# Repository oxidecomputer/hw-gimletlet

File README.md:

# hw-gimletlet
More full-featured breakout board for the STM32H7, including many expansion headers for daughter boards. 

In active use for Hubris development and as a Swiss Army Knife around the lab.  Generally
when someone is speaking about a "gimletlet" the mean gimletlet2 "Glorified Gimletlet" as
a *vanishingly* small number of gimletlet1's were built and used for some very early network
bring-up.

Some [design notes](docs/gimletlet-2.mkdn) for gimletlet2
More [design notes](docs/gimletlet.mkdn) for gimletlet2

Some [mechanical specs](docs/gimletlet-mechanical.pdf)

# Bonus boards

## gimletlet-1
 The OG gimletlet.  Same CPU, nothing else is the same :)

*very limited use, very limited quantity*

[Subfolder](gimletlet1)

## management network bringup

*very limited use, very limited quantity*

Pairs with the gimletlet-1

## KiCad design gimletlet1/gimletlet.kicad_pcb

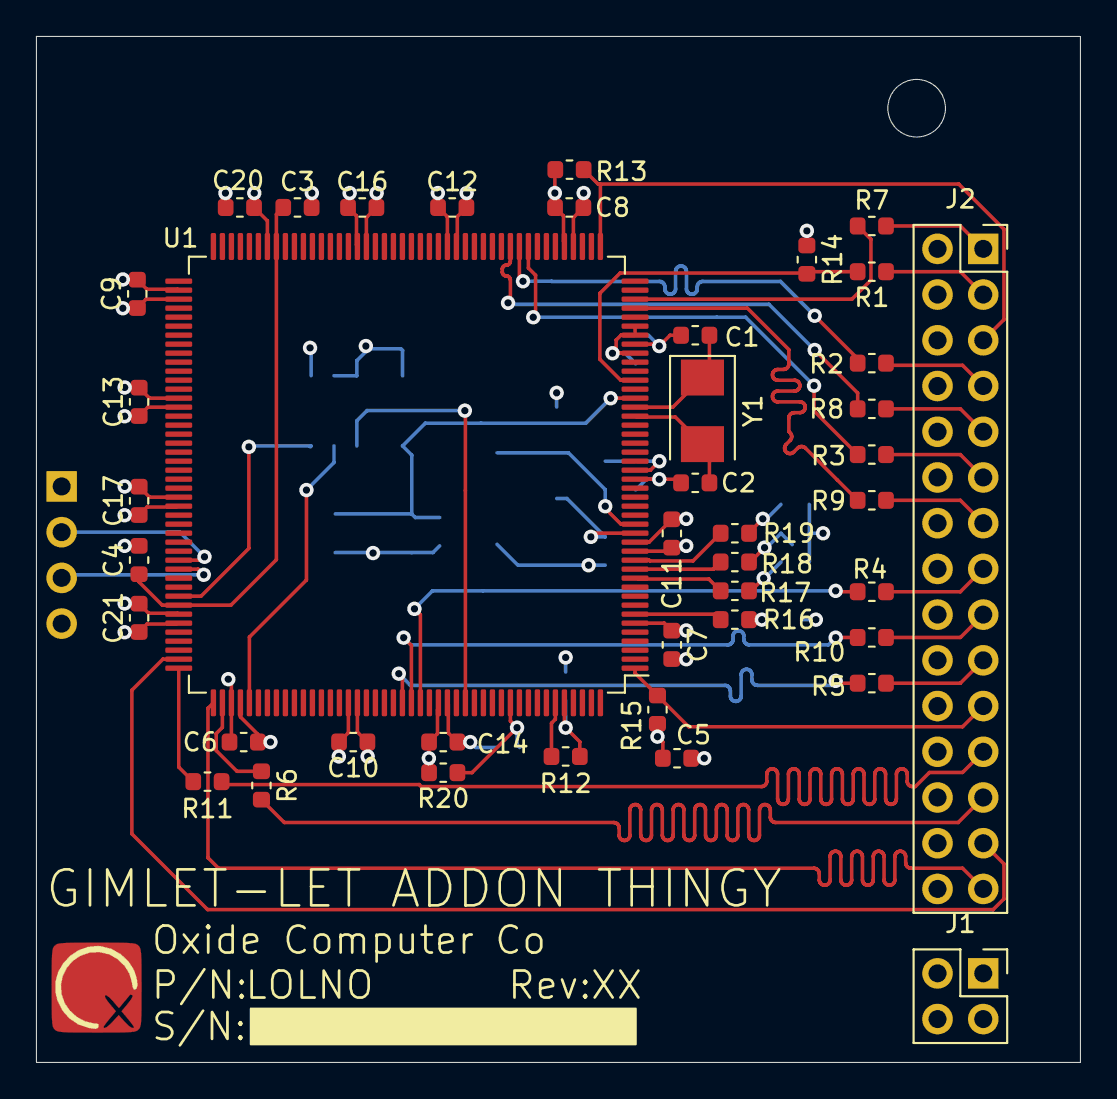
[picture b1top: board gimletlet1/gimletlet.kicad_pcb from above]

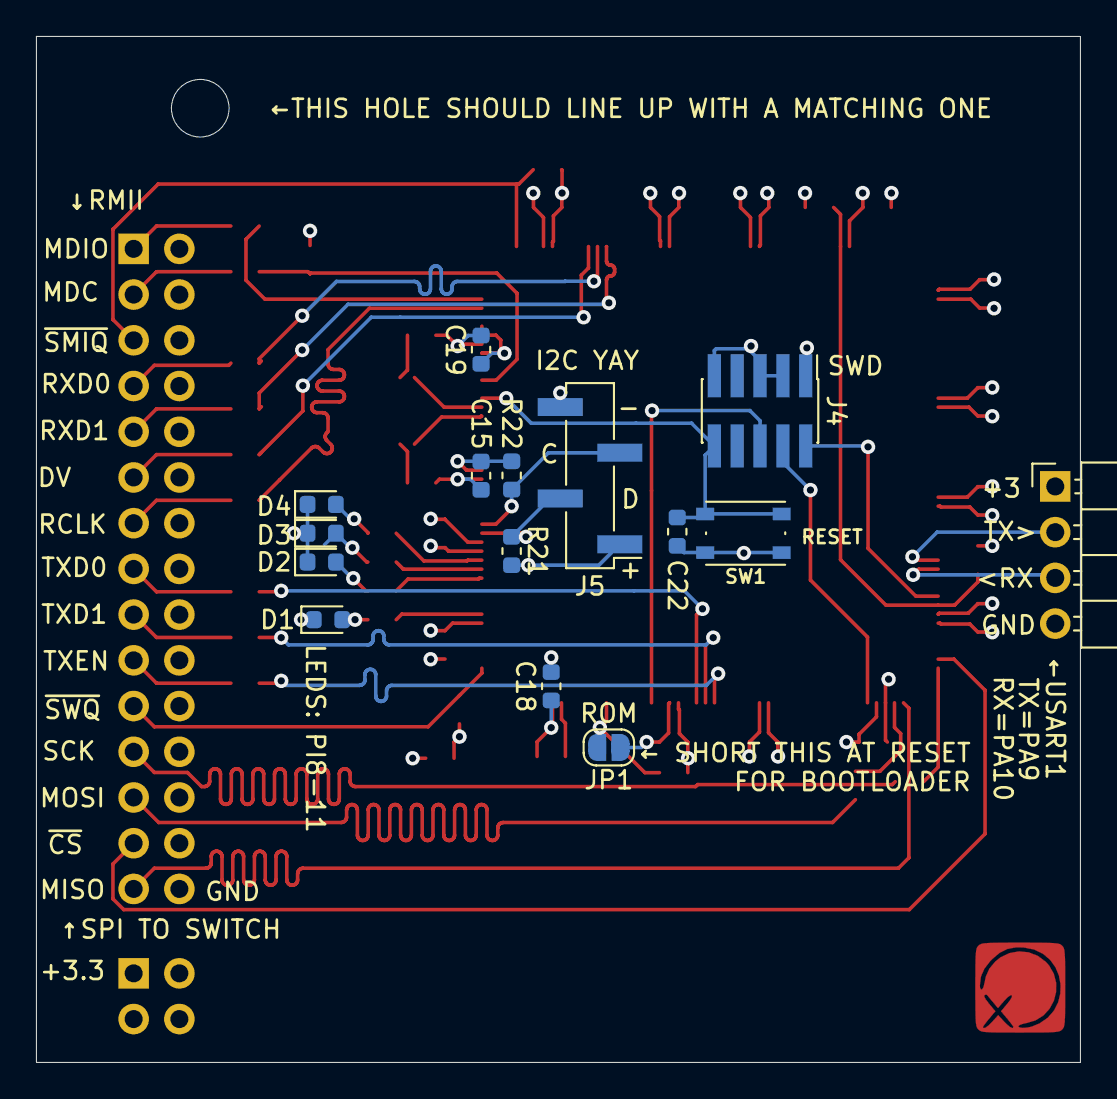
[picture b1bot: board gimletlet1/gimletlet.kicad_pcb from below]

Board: 4 copper layers, 58.0 x 57.0 mm, 59 parts (16 on the bottom side), 49 nets.

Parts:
C1, C2: 11p; C_0603_1608Metric
C3, C4: 2µ2 100mR; C_0603_1608Metric
C5: 4µ7; C_0603_1608Metric
C6, C7, C8, C9, C10, C11, C12, C13, C14, C15, C16, C17, C18, C19, C20, C21, C22: 0µ1; C_0603_1608Metric
D1, D2, D3, D4: LED; LED_0603_1608Metric
FID1: LOLNO; Oxide_Board_Identifier_33x7mm
H1: MountingHole; MountingHole_3.2mm_M3
J1: Conn_02x16_Odd_Even; PinSocket_2x02_P2.54mm_Vertical
J2: Conn_02x15_Odd_Even; PinSocket_2x15_P2.54mm_Vertical
J3: Conn_01x04; PinHeader_1x04_P2.54mm_Horizontal
J4: SWD; PinHeader_2x05_P1.27mm_Vertical_SMD
J5: I2C; PinHeader_1x04_P2.54mm_Vertical_SMD_Pin1Left
JP1: ROM; SolderJumper-2_P1.3mm_Open_RoundedPad1.0x1.5mm
R1, R2, R3, R4, R5, R6, R7, R8, R9, R10, R11: 22; R_0603_1608Metric
R12, R20, R21, R22: 10k; R_0603_1608Metric
R13, R14, R15: 100k; R_0603_1608Metric
R16, R17, R18, R19: 68; R_0603_1608Metric
SW1: RESET; PTS815
U1: STM32H753IITx; LQFP-176_24x24mm_P0.5mm
Y1: 8MHz; Crystal_SMD_5032-2Pin_5.0x3.2mm

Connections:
+3V3: C5.1, C6.1, C7.1, C8.1, C9.1, C10.1, C11.1, C12.1, C13.1, C14.1, C15.1, C16.1, C17.1, C18.1, C19.1, C20.1, C21.1, J1.1, J1.3, J3.1, J4.1, J5.1, JP1.1, R12.2, R13.1, R14.1, R15.1, R21.2, R22.2, U1.6, U1.15, U1.23, U1.36, U1.38, U1.39, U1.49, U1.62, U1.72, U1.82, U1.91, U1.103, U1.114, U1.127, U1.136, U1.149, U1.159, U1.172
/BOOT0: JP1.2, R20.1, U1.166
/LED0: R16.2, U1.7
/LED1: R17.2, U1.11
/LED2: R18.2, U1.12
/LED3: R19.2, U1.13
/MDC: R1.1, R14.2, U1.33
/MDIO: R7.1, U1.42
/OSC_IN: C2.1, U1.29, Y1.2
/OSC_OUT: C1.1, U1.30, Y1.1
/RMII_CRS_DV: R3.1, U1.53
/RMII_REF_CLK: R9.1, U1.41
/RMII_RXD0: R2.1, U1.54
/RMII_RXD1: R8.1, U1.55
/RMII_TXD0: R4.1, U1.156
/RMII_TXD1: R10.1, U1.155
/RMII_TXEN: R5.1, U1.154
/SCL: J5.3, R22.1, U1.17
/SDA: J5.2, R21.1, U1.16
/SPI2_MISO: J2.29, U1.133
/SPI2_MOSI: R6.1, U1.134
/SPI2_SCK: R11.1, U1.132
/SWCLK: J4.4, U1.137
/SWDIO: J4.2, U1.124
/SWO: J4.6, U1.161
/USART1_RX: J3.3, U1.121
/USART1_TX: J3.2, U1.120
/X_MDC: J2.3, R1.2
/X_MDIO: J2.1, R7.2
/X_RMII_CRS_DV: J2.11, R3.2
/X_RMII_REFCLK: J2.13, R9.2
/X_RMII_RXD0: J2.7, R2.2
/X_RMII_RXD1: J2.9, R8.2
/X_RMII_TXD0: J2.15, R4.2
/X_RMII_TXD1: J2.17, R10.2
/X_RMII_TXEN: J2.19, R5.2
/X_SPI_MOSI: J2.25, R6.2
/X_SPI_SCK: J2.23, R11.2
/~RST: C22.1, J4.10, SW1.1, U1.31
/~SMI_IRQ: J2.5, R13.2, U1.45
/~SPI2_CS0: J2.27, U1.131
/~SW_IRQ: J2.21, R15.2, U1.1
GND: C1.2, C2.2, C3.2, C4.2, C5.2, C6.2, C7.2, C8.2, C9.2, C10.2, C11.2, C12.2, C13.2, C14.2, C15.2, C16.2, C17.2, C18.2, C19.2, C20.2, C21.2, C22.2, D1.1, D2.1, D3.1, D4.1, J2.2, J2.4, J2.6, J2.8, J2.10, J2.12, J2.14, J2.16, J2.18, J2.20, J2.22, J2.24, J2.26, J2.28, J2.30, J3.4, J4.3, J4.5, J4.9, J5.4, R20.2, SW1.2, U1.14, U1.22, U1.37, U1.48, U1.61, U1.71, U1.90, U1.102, U1.113, U1.126, U1.135, U1.148, U1.158
unnamed: C3.1, C4.1, U1.81, U1.125
unnamed: D1.2, R16.1
unnamed: D2.2, R17.1
unnamed: D3.2, R18.1
unnamed: D4.2, R19.1
unnamed: R12.1, U1.171

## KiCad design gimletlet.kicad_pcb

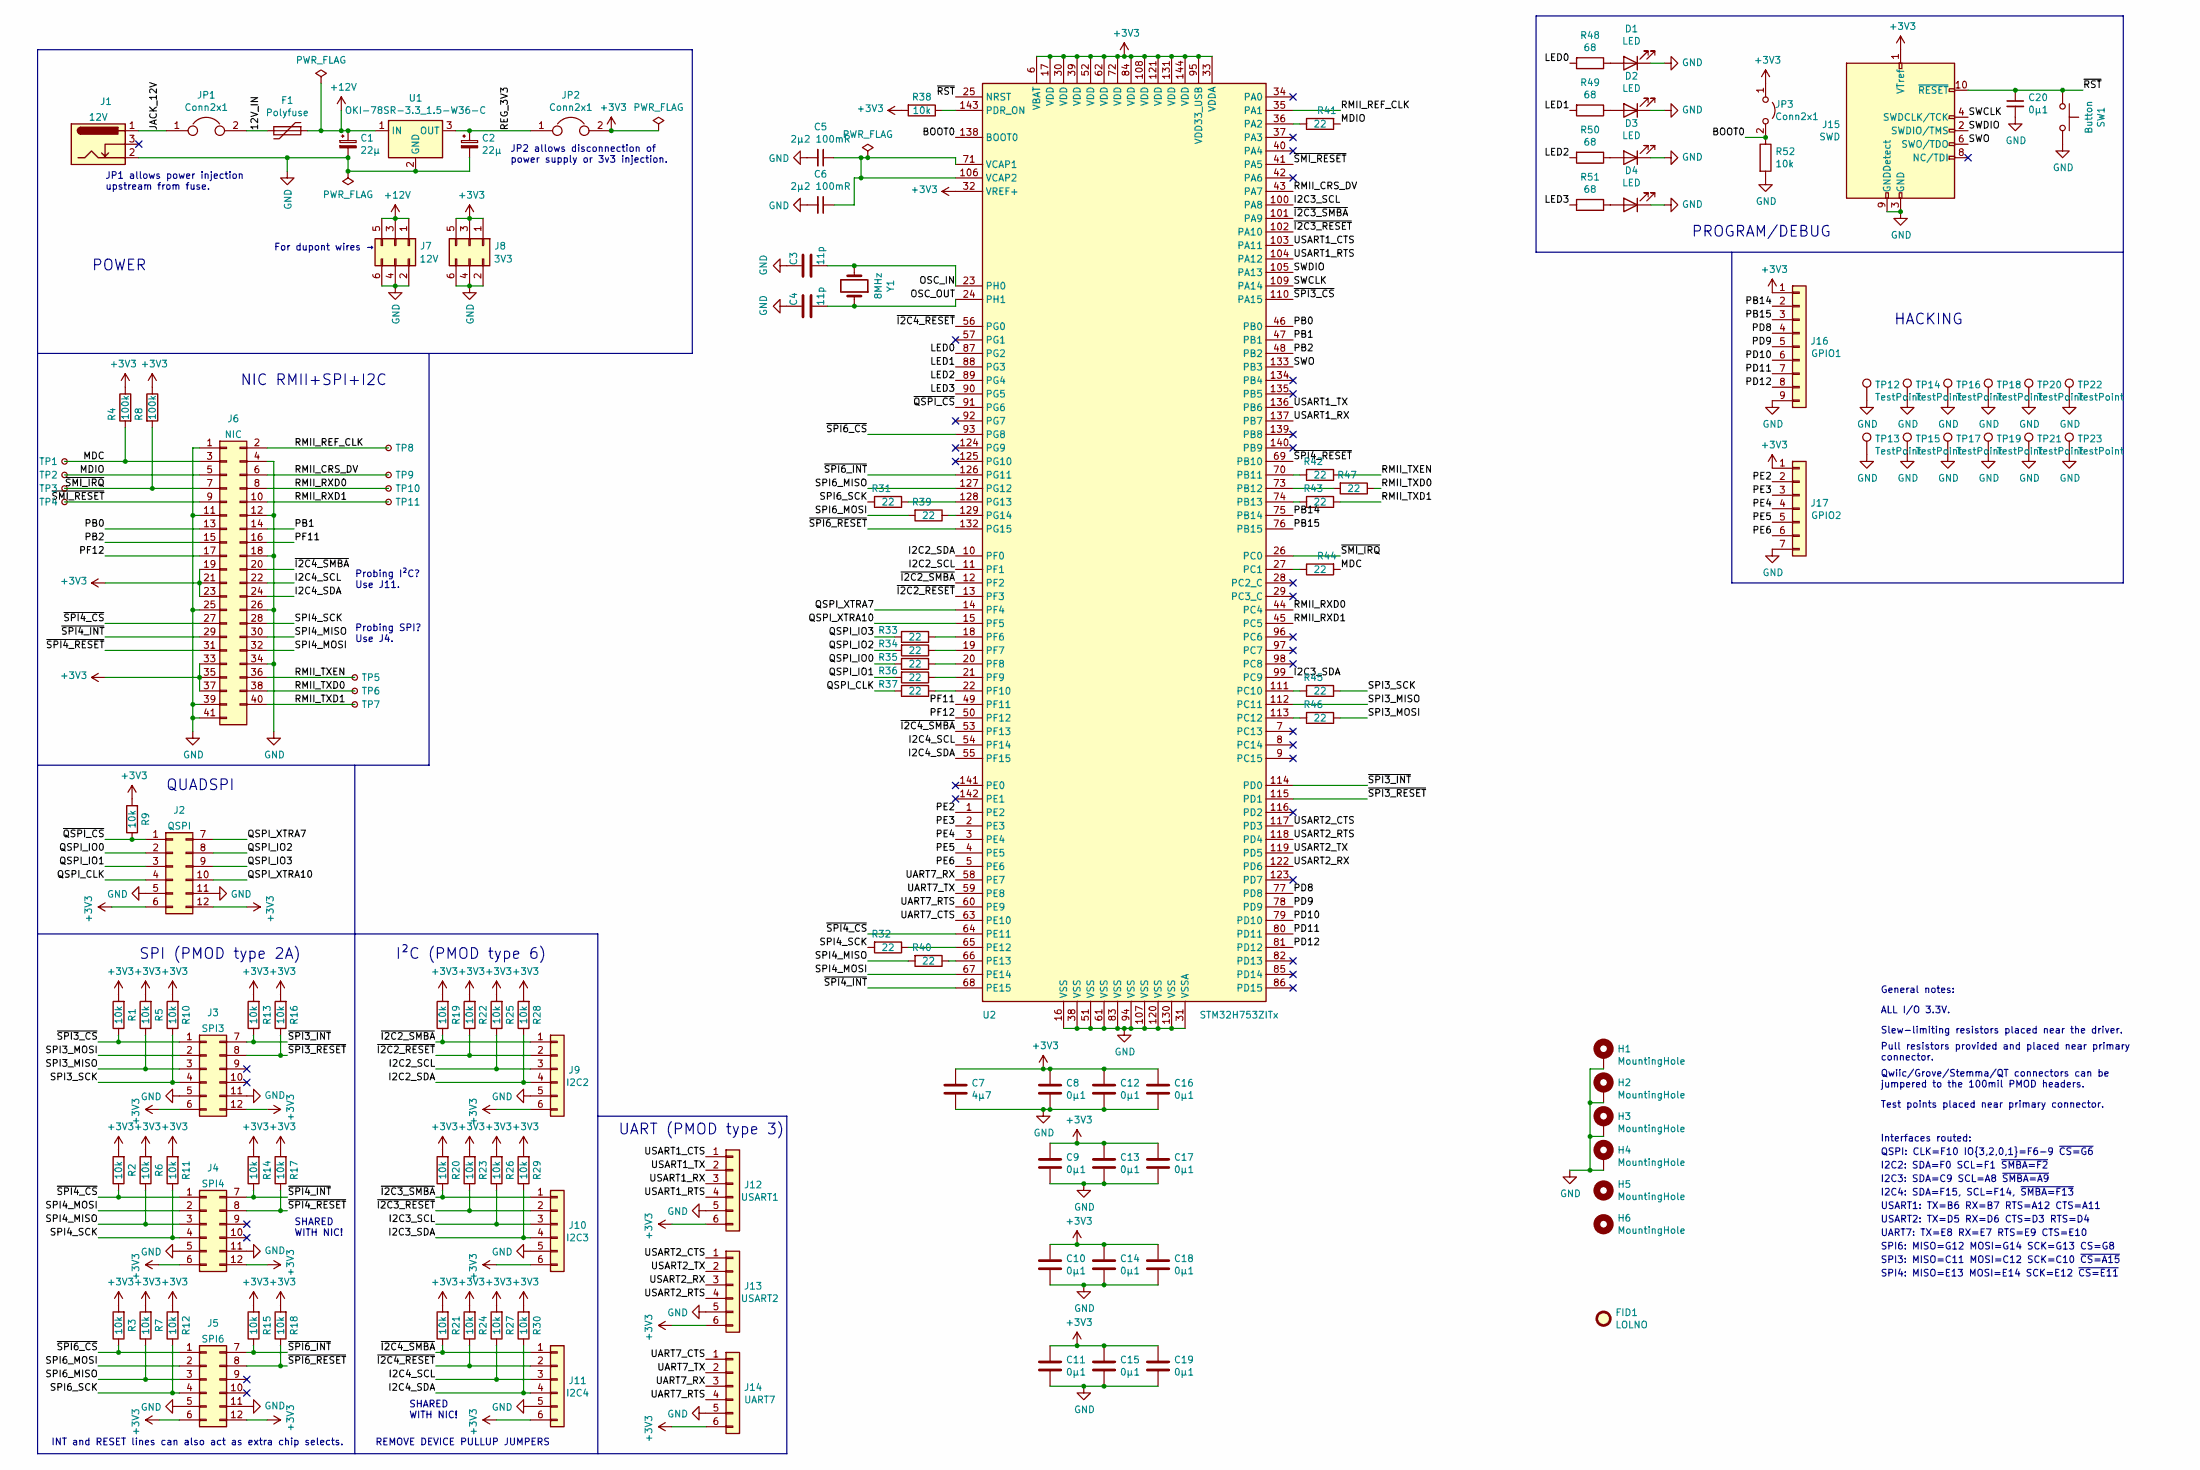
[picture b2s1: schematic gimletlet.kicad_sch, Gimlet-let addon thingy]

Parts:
C1, C2: 22µ; CP_EIA-7343-31_Kemet-D; MPN T491D226K020AT7280
C3, C4: 11p; C_0603_1608Metric; MPN C0603C110J5GACTU
C5, C6: 2µ2 100mR; C_0603_1608Metric; MPN C0603C225K4PACTU
C7: 4µ7; C_0603_1608Metric; MPN CL10A475KQ8NNNC
C8, C9, C10, C11, C12, C13, C14, C15, C16, C17, C18, C19, C20: 0µ1; C_0603_1608Metric; MPN C0603C104M4RACTU
D1: LED; LED_0603_1608Metric; MPN 150060RS75000
D2: LED; LED_0603_1608Metric; MPN 150060AS75000
D3: LED; LED_0603_1608Metric; MPN 150060GS75000
D4: LED; LED_0603_1608Metric; MPN 150060BS75000
F1: Polyfuse; Fuse_1812_4532Metric; MPN 1812L200/16DR
FID1: LOLNO; Oxide_Board_Identifier_33x7mm
H1, H2, H3, H4: MountingHole; MountingHole_3.2mm_M3_Pad_Via
H5, H6: MountingHole; MountingHole_3.2mm_M3
J1: BarrelJack; BarrelJack_CUI_PJ-036AH-SMT_Horizontal; MPN PJ-036AH-SMT-TR
J2, J3, J4, J5: Conn6x2; PMOD_12pin_host_horizontal; MPN PPTC062LJBN-RC
J6: Conn41x2; Hirose_DF9-41S-1V(69)_2Rows_41Pin-2MP_P1.0mm_Vertical; MPN DF9-41S-1V(32)
J7, J8: Conn3x2; PinSocket_2x03_P2.54mm_Vertical; MPN RS2-06-G
J9, J10, J11, J12, J13, J14: Conn6x1; PMOD_6pin_host_horizontal; MPN FR20206HBNN
J15: SWD; PinHeader_2x05_P1.27mm_Vertical_SMD; MPN FTSH-105-01-F-DV-K
J16: Conn9x1; PinSocket_1x09_P2.54mm_Vertical; MPN RS1-09-G
J17: Conn_01x07; PinSocket_1x07_P2.54mm_Vertical; MPN RS1-07-G
JP1, JP2: Conn2x1; PinHeader_1x02_P2.54mm_Vertical; MPN PH1-02-UA
JP3: Conn2x1; PinHeader_2x01_P2.54mm_Vertical; MPN PH1-02-UA
R1, R2, R3, R5, R6, R7, R9, R10, R11, R12, R13, R14, R15, R16, R17, R18, R19, R20, R21, R22, R23, R24, R25, R26, R27, R28, R29, R30, R38, R52: 10k; R_0603_1608Metric; MPN CR0603-JW-103ELF
R4, R8: 100k; R_0603_1608Metric; MPN CR0603-JW-104ELF
R31, R32, R33, R34, R35, R36, R37, R39, R40, R41, R42, R43, R44, R45, R46, R47: 22; R_0603_1608Metric; MPN CR0603-JW-220ELF
R48, R49, R50, R51: 68; R_0603_1608Metric; MPN CR0603-JW-680ELF
SW1: Button; PTS815; MPN PTS815 SJM 250 SMTR LFS
TP1, TP2, TP3, TP4, TP5, TP6, TP7, TP8, TP9, TP10, TP11: TestPoint_Small; TestPoint_THTPad_D2.0mm_Drill1.0mm
TP12, TP13, TP14, TP15, TP16, TP17, TP18, TP19, TP20, TP21, TP22, TP23: TestPoint; TestPoint_Loop_D3.50mm_Drill1.4mm_Beaded; MPN 5006
U1: OKI-78SR-3.3_1.5-W36-C; Converter_DCDC_muRata_OKI-78SR_Vertical; MPN OKI-78SR-3.3/1.5-W36-C
U2: STM32H753ZITx; LQFP-144_20x20mm_P0.5mm; MPN STM32H753ZIT6
Y1: 8MHz; Crystal_SMD_5032-2Pin_5.0x3.2mm; MPN ECS-80-12-30Q-DS-TR

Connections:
+3V3: C7.1, C8.1, C9.1, C10.1, C11.1, C12.1, C13.1, C14.1, C15.1, C16.1, C17.1, C18.1, C19.1, J2.6, J2.12, J3.6, J3.12, J4.6, J4.12, J5.6, J5.12, J6.19, J6.21, J6.23, J6.33, J6.35, J6.37, J8.1, J8.3, J8.5, J9.6, J10.6, J11.6, J12.6, J13.6, J14.6, J15.1 (VTref), J16.1, J17.1, JP2.2, JP3.1 (A), R1.2, R2.2, R3.2, R4.1, R5.2, R6.2, R7.2, R8.1, R9.2, R10.2, R11.2, R12.2, R13.2, R14.2, R15.2, R16.2, R17.2, R18.2, R19.2, R20.2, R21.2, R22.2, R23.2, R24.2, R25.2, R26.2, R27.2, R28.2, R29.2, R30.2, R38.2, U2.6 (VBAT), U2.17 (VDD), U2.30 (VDD), U2.32 (VREF+), U2.33 (VDDA), U2.39 (VDD), U2.52 (VDD), U2.62 (VDD), U2.72 (VDD), U2.84 (VDD), U2.95 (VDD33_USB), U2.108 (VDD), U2.121 (VDD), U2.131 (VDD), U2.144 (VDD)
+12V: C1.1, F1.1, J7.1, J7.3, J7.5, U1.1 (IN)
/12V_IN: F1.2, JP1.2
/BOOT0: JP3.2 (B), R52.1, U2.138 (BOOT0)
/I2C2_SCL: J9.3, R25.1, U2.11 (PF1)
/I2C2_SDA: J9.4, R28.1, U2.10 (PF0)
/I2C3_SCL: J10.3, R26.1, U2.100 (PA8)
/I2C3_SDA: J10.4, R29.1, U2.99 (PC9)
/I2C4_SCL: J6.22, J11.3, R27.1, U2.54 (PF14)
/I2C4_SDA: J6.24, J11.4, R30.1, U2.55 (PF15)
/JACK_12V: J1.1, JP1.1
/LED0: R48.2, U2.87 (PG2)
/LED1: R49.2, U2.88 (PG3)
/LED2: R50.2, U2.89 (PG4)
/LED3: R51.2, U2.90 (PG5)
/MDC: J6.3, R4.2, R44.2, TP1.1
/MDIO: J6.5, R41.2, TP2.1
/OSC_IN: C3.1, U2.23 (PH0), Y1.2
/OSC_OUT: C4.1, U2.24 (PH1), Y1.1
/PB0: J6.13, U2.46 (PB0)
/PB1: J6.14, U2.47 (PB1)
/PB2: J6.15, U2.48 (PB2)
/PB14: J16.2, U2.75 (PB14)
/PB15: J16.3, U2.76 (PB15)
/PD8: J16.4, U2.77 (PD8)
/PD9: J16.5, U2.78 (PD9)
/PD10: J16.6, U2.79 (PD10)
/PD11: J16.7, U2.80 (PD11)
/PD12: J16.8, U2.81 (PD12)
/PE2: J17.2, U2.1 (PE2)
/PE3: J17.3, U2.2 (PE3)
/PE4: J17.4, U2.3 (PE4)
/PE5: J17.5, U2.4 (PE5)
/PE6: J17.6, U2.5 (PE6)
/PF11: J6.16, U2.49 (PF11)
/PF12: J6.17, U2.50 (PF12)
/QSPI_CLK: J2.4, R37.2
/QSPI_IO0: J2.2, R35.2
/QSPI_IO1: J2.3, R36.2
/QSPI_IO2: J2.8, R34.2
/QSPI_IO3: J2.9, R33.2
/QSPI_XTRA7: J2.7, U2.14 (PF4)
/QSPI_XTRA10: J2.10, U2.15 (PF5)
/REG_3V3: C2.1, JP2.1, U1.3 (OUT)
/RMII_CRS_DV: J6.6, TP9.1, U2.43 (PA7)
/RMII_REF_CLK: J6.2, TP8.1, U2.35 (PA1)
/RMII_RXD0: J6.8, TP10.1, U2.44 (PC4)
/RMII_RXD1: J6.10, TP11.1, U2.45 (PC5)
/RMII_TXD0: J6.38, R47.1, TP6.1
/RMII_TXD1: J6.40, R43.1, TP7.1
/RMII_TXEN: J6.36, R42.1, TP5.1
/SPI3_MISO: J3.3, R5.1, U2.112 (PC11)
/SPI3_MOSI: J3.2, R46.1
/SPI3_SCK: J3.4, R10.1, R45.1
/SPI4_MISO: J4.3, J6.30, R6.1, R40.2
/SPI4_MOSI: J4.2, J6.32, U2.67 (PE14)
/SPI4_SCK: J4.4, J6.28, R11.1, R32.2
/SPI6_MISO: J5.3, R7.1, U2.127 (PG12)
/SPI6_MOSI: J5.2, R39.2
/SPI6_SCK: J5.4, R12.1, R31.2
/SWCLK: J15.4 (SWDCLK/TCK), U2.109 (PA14)
/SWDIO: J15.2 (SWDIO/TMS), U2.105 (PA13)
/SWO: J15.6 (SWO/TDO), U2.133 (PB3)
/UART7_CTS: J14.1, U2.63 (PE10)
/UART7_RTS: J14.4, U2.60 (PE9)
/UART7_RX: J14.3, U2.58 (PE7)
/UART7_TX: J14.2, U2.59 (PE8)
/USART1_CTS: J12.1, U2.103 (PA11)
/USART1_RTS: J12.4, U2.104 (PA12)
/USART1_RX: J12.3, U2.137 (PB7)
/USART1_TX: J12.2, U2.136 (PB6)
/USART2_CTS: J13.1, U2.117 (PD3)
/USART2_RTS: J13.4, U2.118 (PD4)
/USART2_RX: J13.3, U2.122 (PD6)
/USART2_TX: J13.2, U2.119 (PD5)
/~I2C2_RESET: J9.2, R22.1, U2.13 (PF3)
/~I2C2_SMBA: J9.1, R19.1, U2.12 (PF2)
/~I2C3_RESET: J10.2, R23.1, U2.102 (PA10)
/~I2C3_SMBA: J10.1, R20.1, U2.101 (PA9)
/~I2C4_RESET: J11.2, R24.1, U2.56 (PG0)
/~I2C4_SMBA: J6.20, J11.1, R21.1, U2.53 (PF13)
/~QSPI_CS: J2.1, R9.1, U2.91 (PG6)
/~RST: C20.1, J15.10 (~RESET), SW1.1, U2.25 (NRST)
/~SMI_IRQ: J6.7, R8.2, TP3.1, U2.26 (PC0)
/~SMI_RESET: J6.9, TP4.1, U2.41 (PA5)
/~SPI3_CS: J3.1, R1.1, U2.110 (PA15)
/~SPI3_INT: J3.7, R13.1, U2.114 (PD0)
/~SPI3_RESET: J3.8, R16.1, U2.115 (PD1)
/~SPI4_CS: J4.1, J6.27, R2.1, U2.64 (PE11)
/~SPI4_INT: J4.7, J6.29, R14.1, U2.68 (PE15)
/~SPI4_RESET: J4.8, J6.31, R17.1, U2.69 (PB10)
/~SPI6_CS: J5.1, R3.1, U2.93 (PG8)
/~SPI6_INT: J5.7, R15.1, U2.126 (PG11)
/~SPI6_RESET: J5.8, R18.1, U2.132 (PG15)
GND: C1.2, C2.2, C3.2, C4.2, C5.2, C6.2, C7.2, C8.2, C9.2, C10.2, C11.2, C12.2, C13.2, C14.2, C15.2, C16.2, C17.2, C18.2, C19.2, C20.2, D1.1 (K), D2.1 (K), D3.1 (K), D4.1 (K), H1.1, H2.1, H3.1, H4.1, J1.2, J2.5, J2.11, J3.5, J3.11, J4.5, J4.11, J5.5, J5.11, J6.1, J6.4, J6.11, J6.12, J6.18, J6.25, J6.26, J6.34, J6.39, J6.41, J7.2, J7.4, J7.6, J8.2, J8.4, J8.6, J9.5, J10.5, J11.5, J12.5, J13.5, J14.5, J15.3 (GND), J15.5 (GND), J15.9 (GNDDetect), J16.9, J17.7, R52.2, SW1.2, TP12.1, TP13.1, TP14.1, TP15.1, TP16.1, TP17.1, TP18.1, TP19.1, TP20.1, TP21.1, TP22.1, TP23.1, U1.2 (GND), U2.16 (VSS), U2.31 (VSSA), U2.38 (VSS), U2.51 (VSS), U2.61 (VSS), U2.83 (VSS), U2.94 (VSS), U2.107 (VSS), U2.120 (VSS), U2.130 (VSS)
unnamed: C5.1, C6.1, U2.71 (VCAP1), U2.106 (VCAP2)
unnamed: D1.2 (A), R48.1
unnamed: D2.2 (A), R49.1
unnamed: D3.2 (A), R50.1
unnamed: D4.2 (A), R51.1
unnamed: R31.1, U2.128 (PG13)
unnamed: R32.1, U2.65 (PE12)
unnamed: R33.1, U2.18 (PF6)
unnamed: R34.1, U2.19 (PF7)
unnamed: R35.1, U2.20 (PF8)
unnamed: R36.1, U2.21 (PF9)
unnamed: R37.1, U2.22 (PF10)
unnamed: R38.1, U2.143 (PDR_ON)
unnamed: R39.1, U2.129 (PG14)
unnamed: R40.1, U2.66 (PE13)
unnamed: R41.1, U2.36 (PA2)
unnamed: R42.2, U2.70 (PB11)
unnamed: R43.2, U2.74 (PB13)
unnamed: R44.1, U2.27 (PC1)
unnamed: R45.2, U2.111 (PC10)
unnamed: R46.2, U2.113 (PC12)
unnamed: R47.2, U2.73 (PB12)

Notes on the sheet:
POWER
SPI4: MISO=E13 MOSI=E14 SCK=E12 ~{CS=E11}
Probing I²C? Use J11.
Slew-limiting resistors placed near the driver.
SPI (PMOD type 2A)
JP2 allows disconnection of power supply or 3v3 injection.
QUADSPI
JP1 allows power injection upstream from fuse.
Test points placed near primary connector.
ALL I/O 3.3V.
SHARED WITH NIC!
REMOVE DEVICE PULLUP JUMPERS
Pull resistors provided and placed near primary connector.
Qwiic/Grove/Stemma/QT connectors can be jumpered to the 100mil PMOD headers.
I2C3: SDA=C9 SCL=A8 ~{SMBA=A9}
SPI6: MISO=G12 MOSI=G14 SCK=G13 CS=G8
Probing SPI? Use J4.
SPI3: MISO=C11 MOSI=C12 SCK=C10 ~{CS=A15}
QSPI: CLK=F10 IO{3,2,0,1}=F6-9 ~{CS=G6}
INT and RESET lines can also act as extra chip selects.
I2C4: SDA=F15, SCL=F14, ~{SMBA=F13}
I²C (PMOD type 6)
UART (PMOD type 3)
USART2: TX=D5 RX=D6 CTS=D3 RTS=D4
USART1: TX=B6 RX=B7 RTS=A12 CTS=A11
NIC RMII+SPI+I2C
Interfaces routed:
For dupont wires →
HACKING
General notes:
PROGRAM/DEBUG
I2C2: SDA=F0 SCL=F1 ~{SMBA=F2}
UART7: TX=E8 RX=E7 RTS=E9 CTS=E10

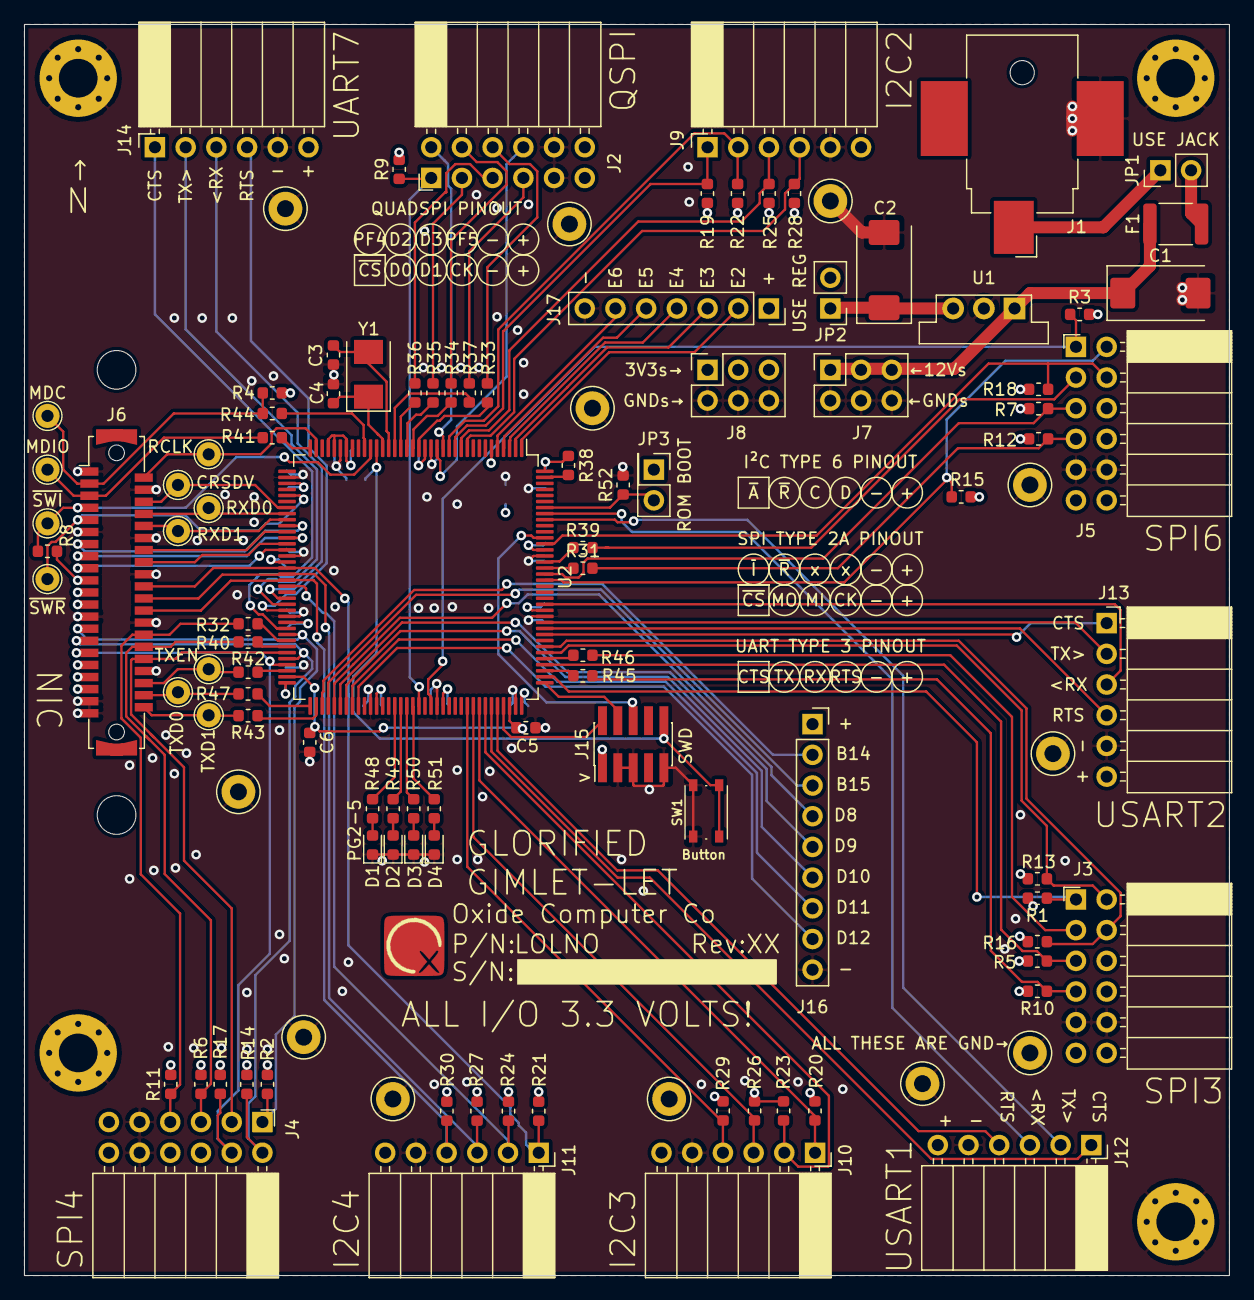
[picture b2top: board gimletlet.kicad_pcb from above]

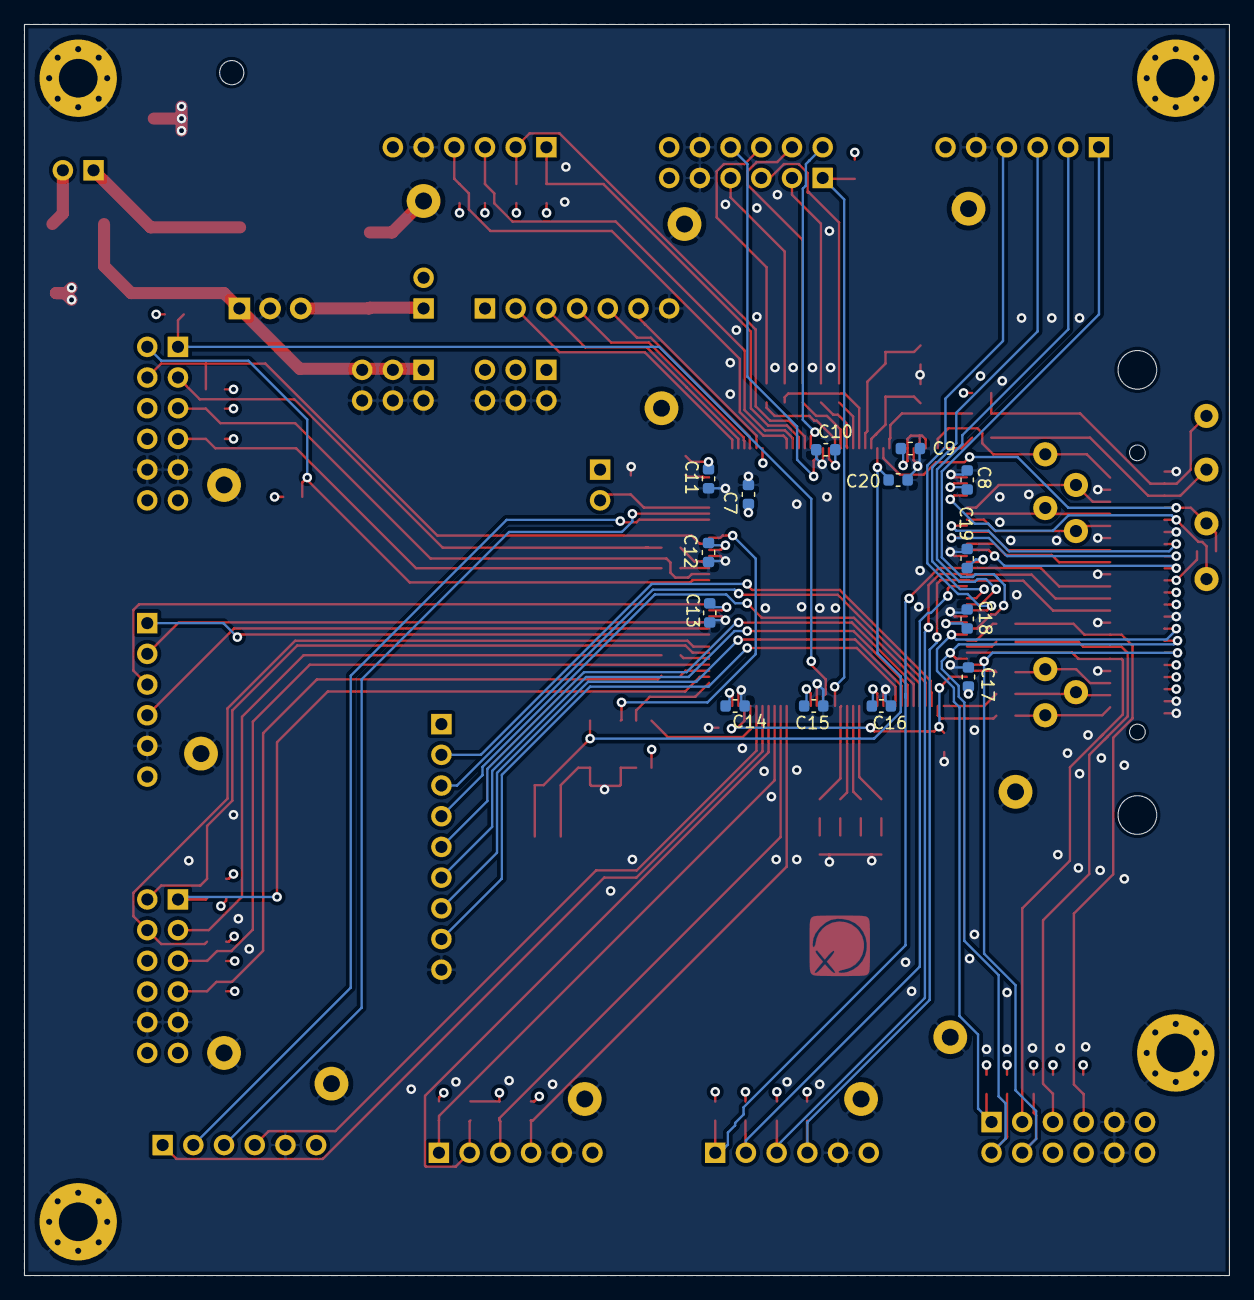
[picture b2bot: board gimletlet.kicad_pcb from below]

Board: 4 copper layers, 99.7 x 103.5 mm, 131 parts (14 on the bottom side), 117 nets.

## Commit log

2023-02-28 Initial commit of gimletlet from gemni repo
